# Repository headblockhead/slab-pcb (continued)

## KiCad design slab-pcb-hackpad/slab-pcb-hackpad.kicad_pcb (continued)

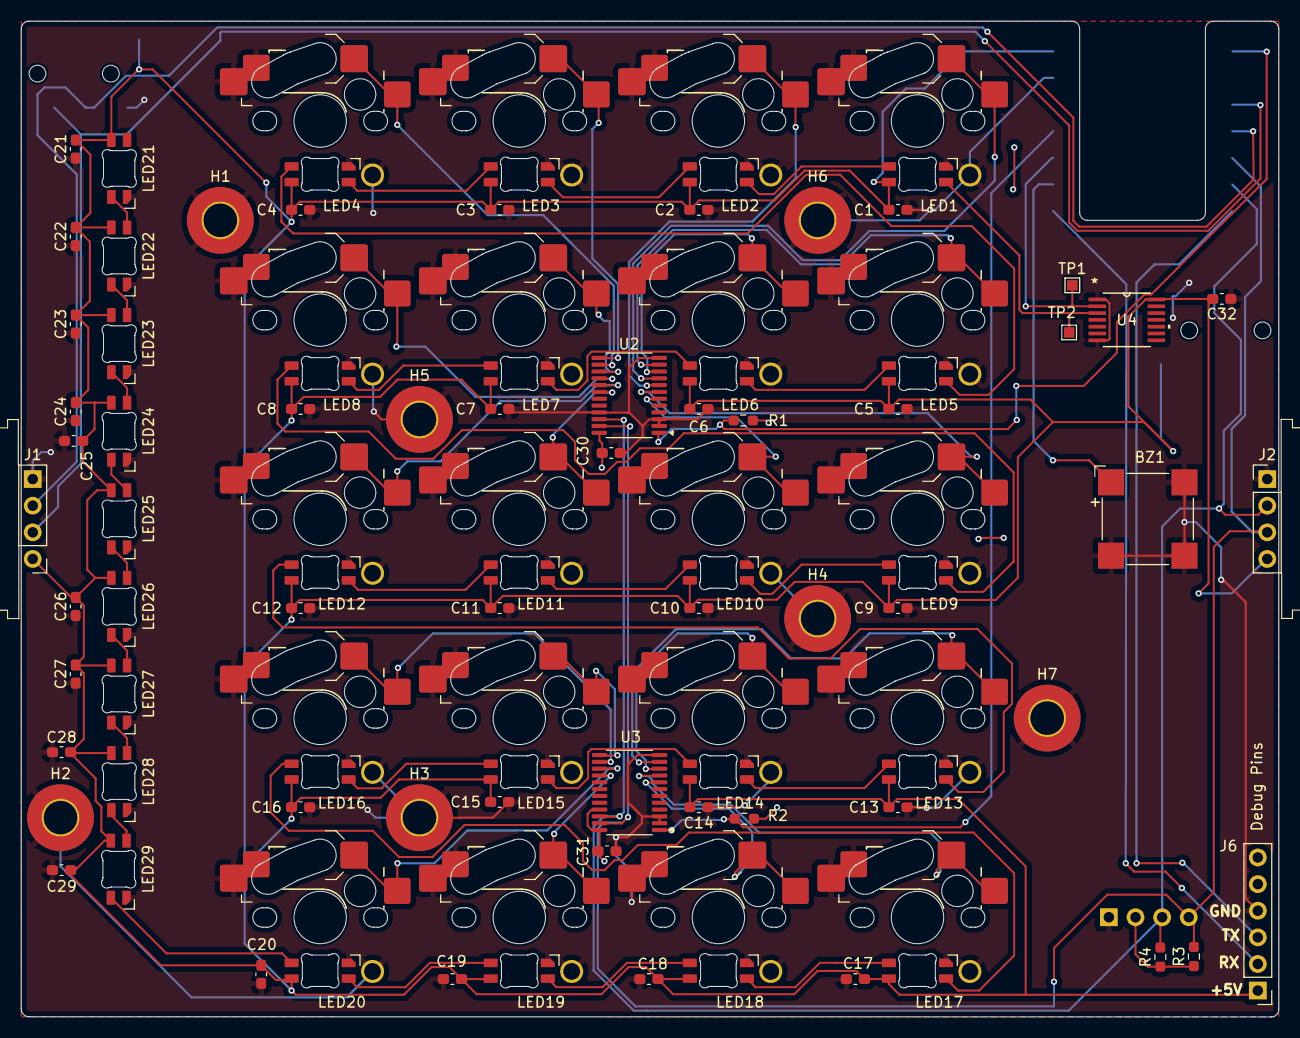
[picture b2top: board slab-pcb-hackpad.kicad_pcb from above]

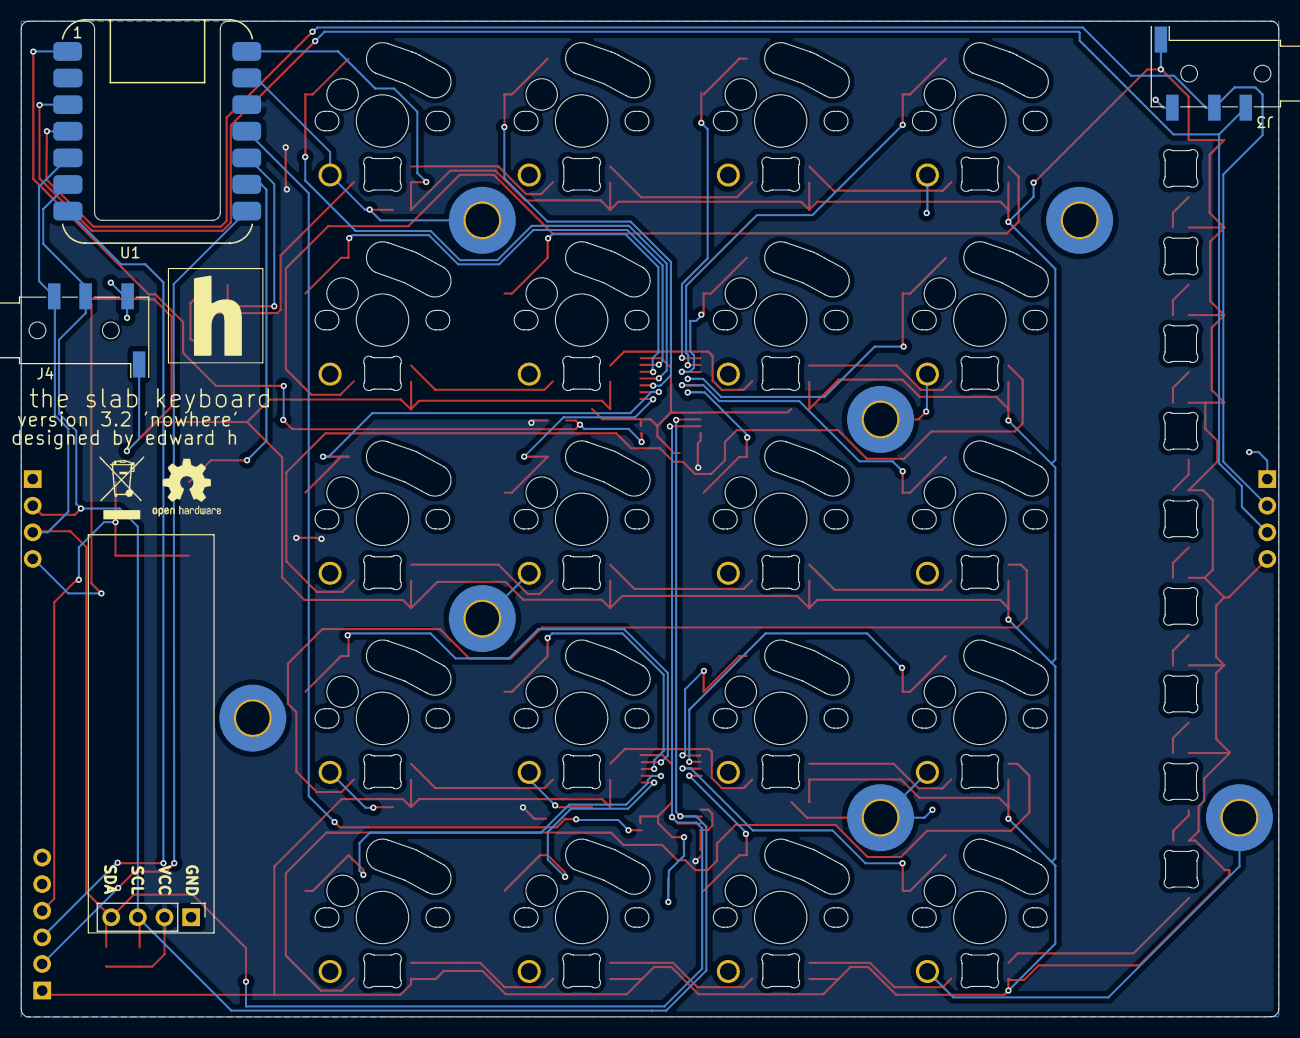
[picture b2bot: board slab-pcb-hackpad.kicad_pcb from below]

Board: 2 copper layers, 120.0 x 95.0 mm, 107 parts (6 on the bottom side), 62 nets.

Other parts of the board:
OSHW: OSHW-Logo2_7.3x6mm_SilkScreen
WEEE: WEEE-Logo_4.2x6mm_SilkScreen

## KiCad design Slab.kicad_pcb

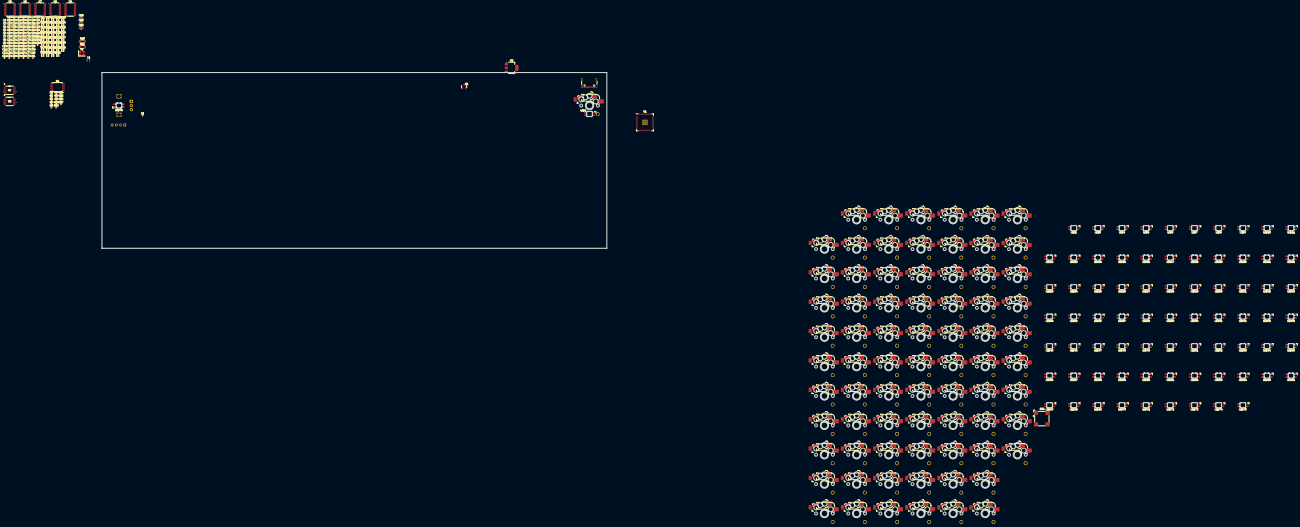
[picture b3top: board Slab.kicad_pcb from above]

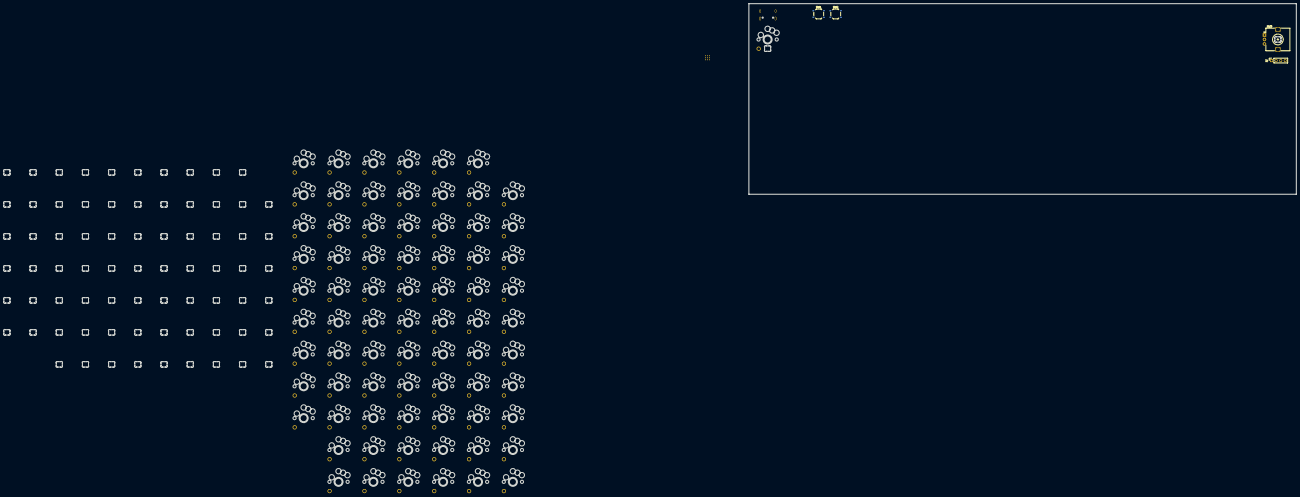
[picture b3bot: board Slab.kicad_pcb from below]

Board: 2 copper layers, 328 parts (4 on the bottom side), 121 nets, no tracks yet.

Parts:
BZ1: Buzzer; MagneticBuzzer_CUI_CMT-8504-100-SMT
C1, C2, C3, C4, C5, C6, C7, C8, C9, C10, C11, C12, C13, C14, C15, C16, C17, C18, C19, C20, C21, C22, C23, C24, C25, C26, C27, C28, C29, C30, C31, C32, C33, C34, C35, C36, C37, C38, C39, C40, C41, C42, C43, C44, C45, C46, C47, C48, C49, C50, C51, C52, C53, C54, C55, C56, C57, C58, C59, C60, C61, C62, C63, C64, C65, C66, C67, C68, C69, C70, C71, C72, C73, C74, C75, C76, C78, C79, C80, C81, C82, C83, C84, C85, C86, C87, C94, C97, C98, C99, C100, C101, C102, C103: 100nF; C_0402_1005Metric
C77, C88: 4.7uF; C_0402_1005Metric
C89, C90: 4.7uF; C_0402_1005Metric_small_pads
C91, C92: 15pF; C_0402_1005Metric
C93: 10u; C_0805_2012Metric
C95, C96: 10uF; C_0805_2012Metric
J1: USB_C_Receptacle_USB2.0_16P; USB_C_Receptacle_GCT_USB4105-xx-A_16P_TopMnt_Horizontal
J2: Conn_01x04; PinSocket_1x04_P2.54mm_Vertical
L1: 3.3u; L_pol_2016
LED1, LED2, LED3, LED4, LED5, LED6, LED7, LED8, LED9, LED10, LED11, LED12, LED13, LED14, LED15, LED16, LED17, LED18, LED19, LED20, LED21, LED22, LED23, LED24, LED25, LED26, LED27, LED28, LED29, LED30, LED31, LED32, LED33, LED34, LED35, LED36, LED37, LED38, LED39, LED40, LED41, LED42, LED43, LED44, LED45, LED46, LED47, LED48, LED49, LED50, LED51, LED52, LED53, LED54, LED55, LED56, LED57, LED58, LED59, LED60, LED61, LED62, LED63, LED64, LED65, LED66, LED67, LED68, LED69, LED70, LED71, LED72, LED73, LED74, LED75: MX_SK6812MINI-E; LED_MX_6028R-ROT_Custom
LED76: SK6812MINI-E; LED_6028R_Custom
MX1, MX2, MX3, MX4, MX5, MX6, MX7, MX8, MX9, MX10, MX11, MX12, MX13, MX14, MX15, MX16, MX17, MX18, MX19, MX20, MX21, MX22, MX23, MX24, MX25, MX26, MX27, MX28, MX29, MX30, MX31, MX32, MX33, MX34, MX35, MX36, MX37, MX38, MX39, MX40, MX41, MX42, MX43, MX44, MX45, MX46, MX47, MX48, MX49, MX50, MX51, MX52, MX53, MX54, MX55, MX56, MX57, MX58, MX59, MX60, MX61, MX62, MX63, MX64, MX65, MX66, MX67, MX68, MX69, MX70, MX71, MX72, MX73, MX74, MX75: SW_MX_CHOC; SW_choc_mx_combined
Q1: MMBT3906; SOT-23
R1: 33; R_0402_1005Metric
R2, R3: 27; R_0402_1005Metric
R4, R5, R12: 1k; R_0402_1005Metric
R6, R13, R14, R15, R16, R17: 10k; R_0402_1005Metric
R7: 5.1k; SN74AHCT125PWR
R8: 5.1k; R_0402_1005Metric
R9: DNF; R_0402_1005Metric
R10, R11: 2.2k; R_1206_3216Metric_Pad1.30x1.75mm_HandSolder
SW1, SW2: SW_Push; SW_Push_1P1T_XKB_TS-1187A
SW3: RotaryEncoder; RotaryEncoder_Alps_EC12E_Vertical_H20mm
TP1: 1V1; TestPoint_Pad_1.0x1.0mm
TP2: USB_DP; TestPoint_Pad_1.0x1.0mm
TP3: USB_DM; TestPoint_Pad_1.0x1.0mm
TP4: XIN; TestPoint_Pad_1.0x1.0mm
TP5: XOUT; TestPoint_Pad_1.0x1.0mm
TP6: RUN; TestPoint_Pad_1.0x1.0mm
TP7, TP8, TP9, TP10, TP12, TP13, TP15, TP17, TP18, TP19, TP20, TP22: TestPoint; TestPoint_Pad_1.0x1.0mm
TP11: 3V3; TestPoint_Pad_1.0x1.0mm
TP14: NPIXEL_SHIFT; TestPoint_Pad_1.0x1.0mm
TP16: NPIXEL_IN; TestPoint_Pad_1.0x1.0mm
TP21: VBUS; TestPoint_Pad_1.0x1.0mm
TP23: CC1; TestPoint_Pad_1.0x1.0mm
TP24: CC2; TestPoint_Pad_1.0x1.0mm
TP25: QSPI_SD0; TestPoint_Pad_1.0x1.0mm
TP26: QSPI_SS; TestPoint_Pad_1.0x1.0mm
TP27: QSPI_SD1; TestPoint_Pad_1.0x1.0mm
TP28: SBU1; TestPoint_Pad_1.0x1.0mm
TP29: SBU2; TestPoint_Pad_1.0x1.0mm
TP30: QSPI_SCLK; TestPoint_Pad_1.0x1.0mm
TP31: QSPI_SD2; TestPoint_Pad_1.0x1.0mm
TP32: QSPI_SD3; TestPoint_Pad_1.0x1.0mm
TP33: ENC_A; TestPoint_Pad_1.0x1.0mm
TP34: ENC_B; TestPoint_Pad_1.0x1.0mm
TP35: EXP1_INT; TestPoint_Pad_1.0x1.0mm
TP36: EXP2_INT; TestPoint_Pad_1.0x1.0mm
TP37: EXP3_INT; TestPoint_Pad_1.0x1.0mm
TP38: EXP4_INT; TestPoint_Pad_1.0x1.0mm
TP39: EXP5_INT; TestPoint_Pad_1.0x1.0mm
U1: RP2350_80QFN; RP2350-QFN-80-1EP_10x10_P0.4mm_EP3.4x3.4mm_ThermalVias
U2: NCP1117-3.3_SOT223; SOT-223-3_TabPin2
U3: SN74AHCT125PWR
U4: W25Q128JVS; SOIC-8_5.23x5.23mm_P1.27mm
U5, U6, U7, U8, U9: PCA9555PW; TSSOP-24_4.4x7.8mm_P0.65mm
Y1: ABM8-272-T3; Crystal_SMD_3225-4Pin_3.2x2.5mm

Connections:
+1V1: C76.1, C77.1, C78.1, C90.1, L1.1, TP1.1, U1.10 (DVDD), U1.32 (DVDD), U1.51 (DVDD), U1.65 (VREG_FB)
+3V3: C79.2, C80.2, C81.2, C82.2, C83.2, C84.2, C85.2, C86.2, C87.2, C89.1, C93.1, C96.1, C97.1, C99.1, C100.1, C101.1, C102.1, C103.1, J2.2, R1.1, R6.2, R9.1, R10.1, R11.1, R13.1, R14.1, R15.1, R16.1, R17.1, TP11.1, U1.5 (IOVDD), U1.15 (IOVDD), U1.24 (IOVDD), U1.29 (IOVDD), U1.41 (IOVDD), U1.50 (IOVDD), U1.59 (ADC_AVDD), U1.60 (IOVDD), U1.64 (VREG_VIN), U1.68 (USB_OTP_VDD), U1.69 (QSPI_IOVDD), U1.76 (IOVDD), U2.2 (VO), U4.8 (VCC), U5.24 (VDD), U6.21 (A0), U6.24 (VDD), U7.2 (A1), U7.24 (VDD), U8.2 (A1), U8.21 (A0), U8.24 (VDD), U9.3 (A2), U9.24 (VDD)
+5V: TP13.1, TP22.1
/BUZZER: R12.1, U1.16 (GPIO16)
/ENCODER_A: SW3.A, TP33.1, U1.79 (GPIO2)
/ENCODER_B: SW3.B, TP34.1, U1.80 (GPIO3)
/ENCODER_LED: LED75.2 (DOUT), LED76.3 (DIN)
/EXPANDER1_INT: R13.2, TP35.1, U1.4 (GPIO7), U5.1 (~INT)
/EXPANDER2_INT: R14.2, TP36.1, U1.6 (GPIO8), U6.1 (~INT)
/EXPANDER3_INT: R15.2, TP37.1, U1.7 (GPIO9), U7.1 (~INT)
/EXPANDER4_INT: R16.2, TP38.1, U1.8 (GPIO10), U8.1 (~INT)
/EXPANDER5_INT: R17.2, TP39.1, U1.9 (GPIO11), U9.1 (~INT)
/I2C1_SCL: J2.3, R11.2, TP20.1, U1.2 (GPIO5), U5.22 (SCL), U6.22 (SCL), U7.22 (SCL), U8.22 (SCL), U9.22 (SCL)
/I2C1_SDA: J2.4, R10.2, TP19.1, U1.1 (GPIO4), U5.23 (SDA), U6.23 (SDA), U7.23 (SDA), U8.23 (SDA), U9.23 (SDA)
/NEOPIXEL_INPUT: LED1.3 (DIN), TP16.1, U3.3 (1Y)
/NEOPIXEL_SHIFTER_INPUT: TP14.1, U1.3 (GPIO6), U3.2 (1A)
/QSPI_SCLK: TP30.1, U1.71 (QSPI_SCLK), U4.6 (CLK)
/QSPI_SD0: TP25.1, U1.72 (QSPI_SD0), U4.5 (DI(IO0))
/QSPI_SD1: TP27.1, U1.74 (QSPI_SD1), U4.2 (DO(IO1))
/QSPI_SD2: TP31.1, U1.73 (QSPI_SD2), U4.3 (IO2)
/QSPI_SD3: TP32.1, U1.70 (QSPI_SD3), U4.7 (IO3)
/QSPI_SS: R4.1, R9.2, TP26.1, U1.75 (QSPI_SS), U4.1 (~CS)
/RESET: R6.1, SW1.1, TP6.1, U1.35 (RUN)
/SWCLK: TP7.1, U1.33 (SWCLK)
/SWD: TP8.1, U1.34 (SWD)
/UART0_RX: TP12.1, U1.78 (GPIO1)
/UART0_TX: TP10.1, U1.77 (GPIO0)
/USB_D+: R2.1, TP2.1
/USB_D-: R3.1, TP3.1
/USB_DM: J1.A7 (D-), J1.B7 (D-)
/USB_DP: J1.A6 (D+), J1.B6 (D+)
/VREG_AVDD: C88.1, R1.2, U1.61 (VREG_AVDD)
/VREG_LX: L1.2, U1.63 (VREG_LX)
/~KEY1: MX1.2, U5.4 (IO0_0)
GND: C1.1, C2.1, C3.1, C4.1, C5.1, C6.1, C7.1, C8.1, C9.1, C10.1, C11.1, C12.1, C13.1, C14.1, C15.1, C16.1, C17.1, C18.1, C19.1, C20.1, C21.1, C22.1, C23.1, C24.1, C25.1, C26.1, C27.1, C28.1, C29.1, C30.1, C31.1, C32.1, C33.1, C34.1, C35.1, C36.1, C37.1, C38.1, C39.1, C40.1, C41.1, C42.1, C43.1, C44.1, C45.1, C46.1, C47.1, C48.1, C49.1, C50.1, C51.1, C52.1, C53.1, C54.1, C55.1, C56.1, C57.1, C58.1, C59.1, C60.1, C61.1, C62.1, C63.1, C64.1, C65.1, C66.1, C67.1, C68.1, C69.1, C70.1, C71.1, C72.1, C73.1, C74.1, C75.1, C76.2, C77.2, C78.2, C79.1, C80.1, C81.1, C82.1, C83.1, C84.1, C85.1, C86.1, C87.1, C88.2, C89.2, C90.2, C91.2, C92.2, C93.2, C94.1, C95.2, C96.2, C97.2, C98.2, C99.2, C100.2, C101.2, C102.2, C103.2, J1.A1 (GND), J1.A12 (GND), J1.B1 (GND), J1.B12 (GND), J1.S1 (SHIELD), J2.1, LED1.4 (VSS), LED2.4 (VSS), LED3.4 (VSS), LED4.4 (VSS), LED5.4 (VSS), LED6.4 (VSS), LED7.4 (VSS), LED8.4 (VSS), LED9.4 (VSS), LED10.4 (VSS), LED11.4 (VSS), LED12.4 (VSS), LED13.4 (VSS), LED14.4 (VSS), LED15.4 (VSS), LED16.4 (VSS), LED17.4 (VSS), LED18.4 (VSS), LED19.4 (VSS), LED20.4 (VSS), LED21.4 (VSS), LED22.4 (VSS), LED23.4 (VSS), LED24.4 (VSS), LED25.4 (VSS), LED26.4 (VSS), LED27.4 (VSS), LED28.4 (VSS), LED29.4 (VSS), LED30.4 (VSS), LED31.4 (VSS), LED32.4 (VSS), LED33.4 (VSS), LED34.4 (VSS), LED35.4 (VSS), LED36.4 (VSS), LED37.4 (VSS), LED38.4 (VSS), LED39.4 (VSS), LED40.4 (VSS), LED41.4 (VSS), LED42.4 (VSS), LED43.4 (VSS), LED44.4 (VSS), LED45.4 (VSS), LED46.4 (VSS), LED47.4 (VSS), LED48.4 (VSS), LED49.4 (VSS), LED50.4 (VSS), LED51.4 (VSS), LED52.4 (VSS), LED53.4 (VSS), LED54.4 (VSS), LED55.4 (VSS), LED56.4 (VSS), LED57.4 (VSS), LED58.4 (VSS), LED59.4 (VSS), LED60.4 (VSS), LED61.4 (VSS), LED62.4 (VSS), LED63.4 (VSS), LED64.4 (VSS), LED65.4 (VSS), LED66.4 (VSS), LED67.4 (VSS), LED68.4 (VSS), LED69.4 (VSS), LED70.4 (VSS), LED71.4 (VSS), LED72.4 (VSS), LED73.4 (VSS), LED74.4 (VSS), LED75.4 (VSS), LED76.4 (VSS), MX1.1, MX2.1, MX3.1, MX4.1, MX5.1, MX6.1, MX7.1, MX8.1, MX9.1, MX10.1, MX11.1, MX12.1, MX13.1, MX14.1, MX15.1, MX16.1, MX17.1, MX18.1, MX19.1, MX20.1, MX21.1, MX22.1, MX23.1, MX24.1, MX25.1, MX26.1, MX27.1, MX28.1, MX29.1, MX30.1, MX31.1, MX32.1, MX33.1, MX34.1, MX35.1, MX36.1, MX37.1, MX38.1, MX39.1, MX40.1, MX41.1, MX42.1, MX43.1, MX44.1, MX45.1, MX46.1, MX47.1, MX48.1, MX49.1, MX50.1, MX51.1, MX52.1, MX53.1, MX54.1, MX55.1, MX56.1, MX57.1, MX58.1, MX59.1, MX60.1, MX61.1, MX62.1, MX63.1, MX64.1, MX65.1, MX66.1, MX67.1, MX68.1, MX69.1, MX70.1, MX71.1, MX72.1, MX73.1, MX74.1, MX75.1, Q1.3 (C), R7.2, R8.2, SW1.2, SW2.2, SW3.C, TP9.1, TP18.1, U1.62 (VREG_PGND), U1.81 (GND), U2.1 (GND), U3.1 (*1OE), U3.7 (GND), U4.4 (GND), U5.2 (A1), U5.3 (A2), U5.12 (VSS), U5.21 (A0), U6.2 (A1), U6.3 (A2), U6.12 (VSS), U7.3 (A2), U7.12 (VSS), U7.21 (A0), U8.3 (A2), U8.12 (VSS), U9.2 (A1), U9.12 (VSS), U9.21 (A0), Y1.2, Y1.4
unnamed: BZ1.2 (-), Q1.2 (E)
unnamed: C92.1, R5.2, Y1.3
unnamed: J1.A5 (CC1), R7.1, TP23.1
unnamed: J1.B5 (CC2), R8.1, TP24.1
unnamed: J1.A8 (SBU1), TP28.1
unnamed: J1.B8 (SBU2), TP29.1
unnamed: LED1.2 (DOUT), LED2.3 (DIN)
unnamed: LED2.2 (DOUT), LED3.3 (DIN)
unnamed: LED3.2 (DOUT), LED4.3 (DIN)
unnamed: LED4.2 (DOUT), LED5.3 (DIN)
unnamed: LED5.2 (DOUT), LED6.3 (DIN)
unnamed: LED6.2 (DOUT), LED7.3 (DIN)
unnamed: LED7.2 (DOUT), LED8.3 (DIN)
unnamed: LED8.2 (DOUT), LED9.3 (DIN)
unnamed: LED9.2 (DOUT), LED10.3 (DIN)
unnamed: LED10.2 (DOUT), LED11.3 (DIN)
unnamed: LED11.2 (DOUT), LED12.3 (DIN)
unnamed: LED12.2 (DOUT), LED13.3 (DIN)
unnamed: LED13.2 (DOUT), LED14.3 (DIN)
unnamed: LED14.2 (DOUT), LED15.3 (DIN)
unnamed: LED15.2 (DOUT), LED16.3 (DIN)
unnamed: LED16.2 (DOUT), LED17.3 (DIN)
unnamed: LED17.2 (DOUT), LED18.3 (DIN)
unnamed: LED18.2 (DOUT), LED19.3 (DIN)
unnamed: LED19.2 (DOUT), LED20.3 (DIN)
unnamed: LED20.2 (DOUT), LED21.3 (DIN)
unnamed: LED21.2 (DOUT), LED22.3 (DIN)
unnamed: LED22.2 (DOUT), LED23.3 (DIN)
unnamed: LED23.2 (DOUT), LED24.3 (DIN)
unnamed: LED24.2 (DOUT), LED25.3 (DIN)
unnamed: LED25.2 (DOUT), LED26.3 (DIN)
unnamed: LED26.2 (DOUT), LED27.3 (DIN)
unnamed: LED27.2 (DOUT), LED28.3 (DIN)
unnamed: LED28.2 (DOUT), LED29.3 (DIN)
unnamed: LED29.2 (DOUT), LED30.3 (DIN)
unnamed: LED30.2 (DOUT), LED31.3 (DIN)
unnamed: LED31.2 (DOUT), LED32.3 (DIN)
unnamed: LED32.2 (DOUT), LED33.3 (DIN)
unnamed: LED33.2 (DOUT), LED34.3 (DIN)
unnamed: LED34.2 (DOUT), LED35.3 (DIN)
unnamed: LED35.2 (DOUT), LED36.3 (DIN)
unnamed: LED36.2 (DOUT), LED37.3 (DIN)
unnamed: LED37.2 (DOUT), LED38.3 (DIN)
unnamed: LED38.2 (DOUT), LED39.3 (DIN)
unnamed: LED39.2 (DOUT), LED40.3 (DIN)
unnamed: LED40.2 (DOUT), LED41.3 (DIN)
unnamed: LED41.2 (DOUT), LED42.3 (DIN)
unnamed: LED42.2 (DOUT), LED43.3 (DIN)
unnamed: LED43.2 (DOUT), LED44.3 (DIN)
unnamed: LED44.2 (DOUT), LED45.3 (DIN)
unnamed: LED45.2 (DOUT), LED46.3 (DIN)
unnamed: LED46.2 (DOUT), LED47.3 (DIN)
unnamed: LED47.2 (DOUT), LED48.3 (DIN)
unnamed: LED48.2 (DOUT), LED49.3 (DIN)
unnamed: LED49.2 (DOUT), LED50.3 (DIN)
unnamed: LED50.2 (DOUT), LED51.3 (DIN)
unnamed: LED51.2 (DOUT), LED52.3 (DIN)
unnamed: LED52.2 (DOUT), LED53.3 (DIN)
unnamed: LED53.2 (DOUT), LED54.3 (DIN)
unnamed: LED54.2 (DOUT), LED55.3 (DIN)
unnamed: LED55.2 (DOUT), LED56.3 (DIN)
unnamed: LED56.2 (DOUT), LED57.3 (DIN)
unnamed: LED57.2 (DOUT), LED58.3 (DIN)
unnamed: LED58.2 (DOUT), LED59.3 (DIN)
unnamed: LED59.2 (DOUT), LED60.3 (DIN)
unnamed: LED60.2 (DOUT), LED61.3 (DIN)
unnamed: LED61.2 (DOUT), LED62.3 (DIN)
unnamed: LED62.2 (DOUT), LED63.3 (DIN)
unnamed: LED63.2 (DOUT), LED64.3 (DIN)
unnamed: LED64.2 (DOUT), LED65.3 (DIN)
unnamed: LED65.2 (DOUT), LED66.3 (DIN)
unnamed: LED66.2 (DOUT), LED67.3 (DIN)
unnamed: LED67.2 (DOUT), LED68.3 (DIN)
unnamed: LED68.2 (DOUT), LED69.3 (DIN)
unnamed: LED69.2 (DOUT), LED70.3 (DIN)
unnamed: LED70.2 (DOUT), LED71.3 (DIN)
unnamed: LED71.2 (DOUT), LED72.3 (DIN)
unnamed: LED72.2 (DOUT), LED73.3 (DIN)
unnamed: LED73.2 (DOUT), LED74.3 (DIN)
unnamed: LED74.2 (DOUT), LED75.3 (DIN)
unnamed: Q1.1 (B), R12.2
unnamed: R3.2, U1.66 (USB_DM)
unnamed: R2.2, U1.67 (USB_DP)
unnamed: C91.1, TP4.1, U1.30 (XIN), Y1.1
unnamed: R5.1, TP5.1, U1.31 (XOUT)
VBUS: BZ1.1 (+), C1.2, C2.2, C3.2, C4.2, C5.2, C6.2, C7.2, C8.2, C9.2, C10.2, C11.2, C12.2, C13.2, C14.2, C15.2, C16.2, C17.2, C18.2, C19.2, C20.2, C21.2, C22.2, C23.2, C24.2, C25.2, C26.2, C27.2, C28.2, C29.2, C30.2, C31.2, C32.2, C33.2, C34.2, C35.2, C36.2, C37.2, C38.2, C39.2, C40.2, C41.2, C42.2, C43.2, C44.2, C45.2, C46.2, C47.2, C48.2, C49.2, C50.2, C51.2, C52.2, C53.2, C54.2, C55.2, C56.2, C57.2, C58.2, C59.2, C60.2, C61.2, C62.2, C63.2, C64.2, C65.2, C66.2, C67.2, C68.2, C69.2, C70.2, C71.2, C72.2, C73.2, C74.2, C75.2, C94.2, C95.1, C98.1, J1.A4 (VBUS), J1.A9 (VBUS), J1.B4 (VBUS), J1.B9 (VBUS), LED1.1 (VDD), LED2.1 (VDD), LED3.1 (VDD), LED4.1 (VDD), LED5.1 (VDD), LED6.1 (VDD), LED7.1 (VDD), LED8.1 (VDD), LED9.1 (VDD), LED10.1 (VDD), LED11.1 (VDD), LED12.1 (VDD), LED13.1 (VDD), LED14.1 (VDD), LED15.1 (VDD), LED16.1 (VDD), LED17.1 (VDD), LED18.1 (VDD), LED19.1 (VDD), LED20.1 (VDD), LED21.1 (VDD), LED22.1 (VDD), LED23.1 (VDD), LED24.1 (VDD), LED25.1 (VDD), LED26.1 (VDD), LED27.1 (VDD), LED28.1 (VDD), LED29.1 (VDD), LED30.1 (VDD), LED31.1 (VDD), LED32.1 (VDD), LED33.1 (VDD), LED34.1 (VDD), LED35.1 (VDD), LED36.1 (VDD), LED37.1 (VDD), LED38.1 (VDD), LED39.1 (VDD), LED40.1 (VDD), LED41.1 (VDD), LED42.1 (VDD), LED43.1 (VDD), LED44.1 (VDD), LED45.1 (VDD), LED46.1 (VDD), LED47.1 (VDD), LED48.1 (VDD), LED49.1 (VDD), LED50.1 (VDD), LED51.1 (VDD), LED52.1 (VDD), LED53.1 (VDD), LED54.1 (VDD), LED55.1 (VDD), LED56.1 (VDD), LED57.1 (VDD), LED58.1 (VDD), LED59.1 (VDD), LED60.1 (VDD), LED61.1 (VDD), LED62.1 (VDD), LED63.1 (VDD), LED64.1 (VDD), LED65.1 (VDD), LED66.1 (VDD), LED67.1 (VDD), LED68.1 (VDD), LED69.1 (VDD), LED70.1 (VDD), LED71.1 (VDD), LED72.1 (VDD), LED73.1 (VDD), LED74.1 (VDD), LED75.1 (VDD), LED76.1 (VDD), TP21.1, U2.3 (VI), U3.14 (VCC)

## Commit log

2024-05-25 feat: first commit
2024-05-25 feat: update symbol and footprint libraries and add more 3D models
2024-05-25 feat: update schematic symbols
2024-05-25 fix: typo in README
2024-05-25 docs: add totals to README
2024-05-25 feat: add gitignore
2024-08-24 Create LICENSE
2024-09-02 feat: init v2 schematic
2024-09-03 feat: add most parts
2024-09-05 feat: add rp2350 footprints+symbols
2024-09-06 feat: rp2350 design mostly complete
2024-09-06 feat: start PCB layout
2024-09-09 feat: layout + track most of board
2024-09-10 feat: almost fully finished design
2024-09-11 feat: slab v2, do not make
2024-09-14 feat: start over with integrated chip
2024-09-18 feat: route board
2024-09-19 feat: start right board
2024-09-21 feat: full left and right boards
2024-09-22 feat: add hackpad
2024-09-22 misc
2024-10-16 fix: inconsistent design
    all modules now share the same design - with updated footprints to
    support both choc+mx PCB mounting holes.
2024-10-16 fix: regen all filled zones, and most DRC
2024-10-20 chore: move shared files to a central directory
2024-10-20 chore: delete unused files
2024-10-25 misc: unknown changes to hackpad
2024-11-04 fix: upside-down magnetic connectors
2024-11-22 misc hackpad changes
2024-11-23 fix: add voltage divider to potentiometer
2024-12-02 use GPLv3
    All further versions of the files here after this commit are licensed under GPLv3. This does not affect previous versions before this commit.
2024-12-04 feat: update
2024-12-07 feat: use slots instead of overlapped drill hits
2024-12-07 chore: move via outside of text
2024-12-09 feat: bump to 3.2
2025-01-05 feat: add nix flake
2025-01-05 ci: add github action
2025-01-16 feat: convert text to polygon
    Original text is stored on User.3, Silkscreen layers now use polygons to
    remove font requirement.
2025-01-29 docs: add README
2025-03-09 feat: add User.6 as printable layout helper
2025-04-16 feat: start on v4, updated: right-hand schematic
2025-04-16 feat: route most of slab-pcb-right
2025-04-16 feat: restart slab-pcb-right routing, allign components
2025-04-17 feat: route keys of slab-right
2025-04-17 feat: finish routing slab-pcb-right
2025-04-18 feat: finialise slab-pcb-right
2025-04-18 feat: rename right to interchange
2025-04-18 feat: add connectors to pcb-right using snap-off mousebites
2025-04-18 docs(README): add purpose of user layers
2025-04-19 feat: round connector pads, add resistor values + silkscreen gfx
2025-04-19 fix(right): delete tiny extra piece of copper
2025-04-19 ci: use 'interchange' instead of 'slab'
2025-04-23 chore: rename slab-pcb-hackpad -> interchange-pcb-hackpad
2025-04-23 feat: create schematic for interchange-pcb-hackpad
    and fix minor spacing issues with capaicitors in interchange-pcb-right
2025-05-05 feat(right): add LCSC part numbers to schematics
2025-12-07 Update LICENSE
2026-05-17 wip: add reverse polarity protection and fix buzzer
2026-05-19 feat(right): add more mounting holes
2026-05-19 chore: update flake.lock
2026-05-25 wip: create testing board
